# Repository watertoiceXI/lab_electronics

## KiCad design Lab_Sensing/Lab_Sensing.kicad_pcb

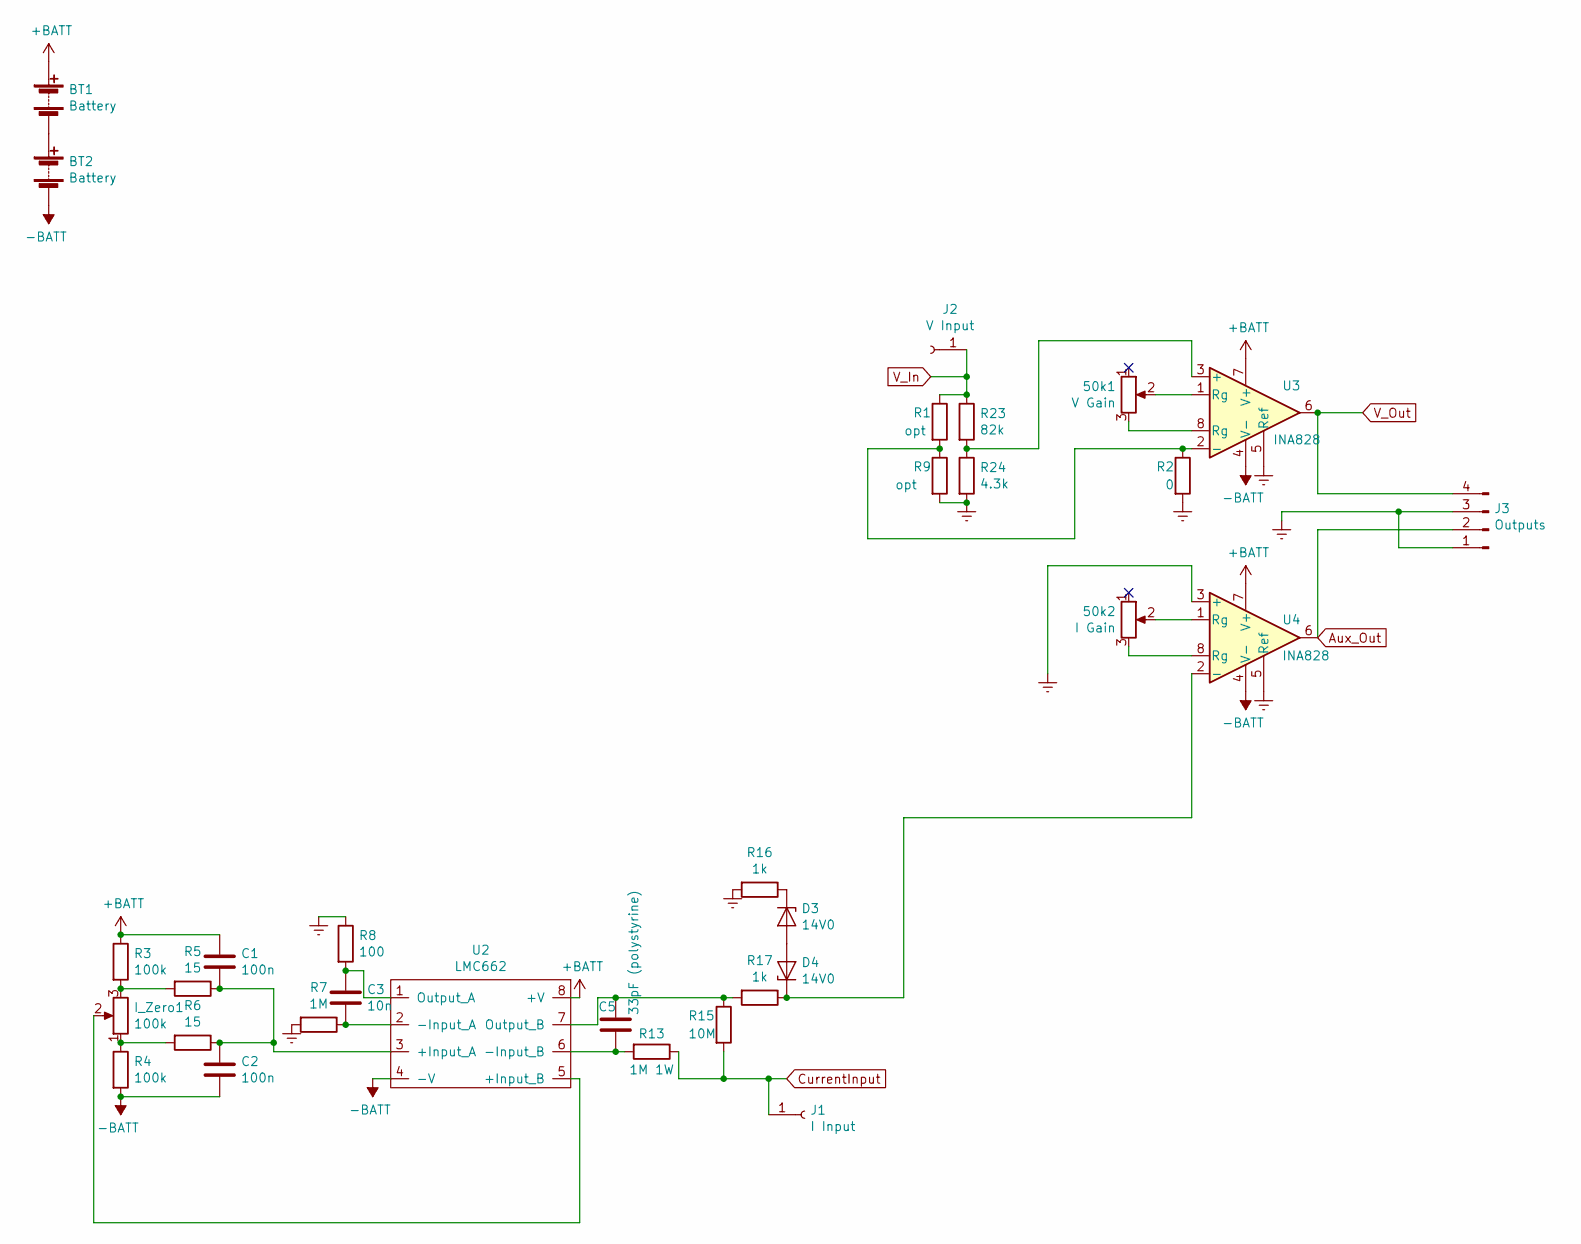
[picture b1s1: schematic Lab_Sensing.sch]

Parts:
50k1: V Gain; Potentiometer_Vishay_T73YP_Vertical
50k2: I Gain; Potentiometer_Vishay_T73YP_Vertical
BT1, BT2: Battery; SolderWirePad_1x02_P3.81mm_Drill1.2mm
C1, C2: 100n; C_0805_2012Metric_Pad1.15x1.40mm_HandSolder
C3: 10n; C_0805_2012Metric_Pad1.15x1.40mm_HandSolder
C5: 33pF (polystyrine); CP_Axial_L11.0mm_D5.0mm_P18.00mm_Horizontal
D3, D4: 14V0; D_SOD-123
I_Zero1: 100k; Potentiometer_Vishay_T73YP_Vertical
J1: I Input; PinHeader_1x01_P2.54mm_Vertical
J2: V Input; PinHeader_1x01_P2.54mm_Vertical
J3: Outputs; PinHeader_1x04_P2.54mm_Vertical
R1, R9: opt; R_Axial_DIN0207_L6.3mm_D2.5mm_P7.62mm_Horizontal
R2: 0; R_Axial_DIN0207_L6.3mm_D2.5mm_P7.62mm_Horizontal
R3, R4: 100k; R_0805_2012Metric
R5, R6: 15; R_0805_2012Metric
R7: 1M; R_0805_2012Metric
R8: 100; R_0805_2012Metric
R13: 1M 1W; R_Axial_DIN0617_L17.0mm_D6.0mm_P20.32mm_Horizontal
R15: 10M; R_Axial_DIN0207_L6.3mm_D2.5mm_P7.62mm_Horizontal
R16, R17: 1k; R_Axial_DIN0207_L6.3mm_D2.5mm_P7.62mm_Horizontal
R23: 82k; R_Axial_DIN0207_L6.3mm_D2.5mm_P7.62mm_Horizontal
R24: 4.3k; R_Axial_DIN0207_L6.3mm_D2.5mm_P7.62mm_Horizontal
U2: LMC662; SOIC-8_3.9x4.9mm_P1.27mm
U3, U4: INA828; SOIC-8_3.9x4.9mm_P1.27mm

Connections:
+BATT: BT1.1 (+), C1.1, R3.1, U2.8 (+V), U3.7 (V+), U4.7 (V+)
-BATT: BT2.2 (-), C2.2, R4.2, U2.4 (-V), U3.4 (V-), U4.4 (V-)
Aux_Out: J3.2, U4.6
CurrentInput: J1.1, R13.1, R15.2
Earth: J3.1, J3.3, R2.2, R7.2, R8.1, R9.2, R16.2, R24.2, U3.5 (Ref), U4.3 (+), U4.5 (Ref)
unnamed 6: 50k1.2, U3.1 (Rg); also elsewhere on the board
unnamed 7: 50k1.3, U3.8 (Rg); also elsewhere on the board
unnamed 9: 50k2.2, U4.1 (Rg); also elsewhere on the board
unnamed 10: 50k2.3, U4.8 (Rg); also elsewhere on the board
unnamed: BT1.2 (-), BT2.1 (+)
unnamed: C1.2, C2.1, R5.1, R6.1, U2.3 (+Input_A)
unnamed: C3.1, R8.2, U2.1 (Output_A)
unnamed: C3.2, R7.1, U2.2 (-Input_A)
unnamed: C5.1, R15.1, R17.2, U2.7 (Output_B)
unnamed: C5.2, R13.2, U2.6 (-Input_B)
unnamed: D3.1 (K), R16.1
unnamed: D3.2 (A), D4.2 (A)
unnamed: D4.1 (K), R17.1, U4.2 (-)
unnamed 20: I_Zero1.1, R4.1, R6.2; also elsewhere on the board
unnamed 21: I_Zero1.2, U2.5 (+Input_B); also elsewhere on the board
unnamed 22: I_Zero1.3, R3.2, R5.2; also elsewhere on the board
unnamed: R1.2, R2.1, R9.1, U3.2 (-)
unnamed: R23.2, R24.1, U3.3 (+)
V_In: J2.1, R1.1, R23.1
V_Out: J3.4, U3.6

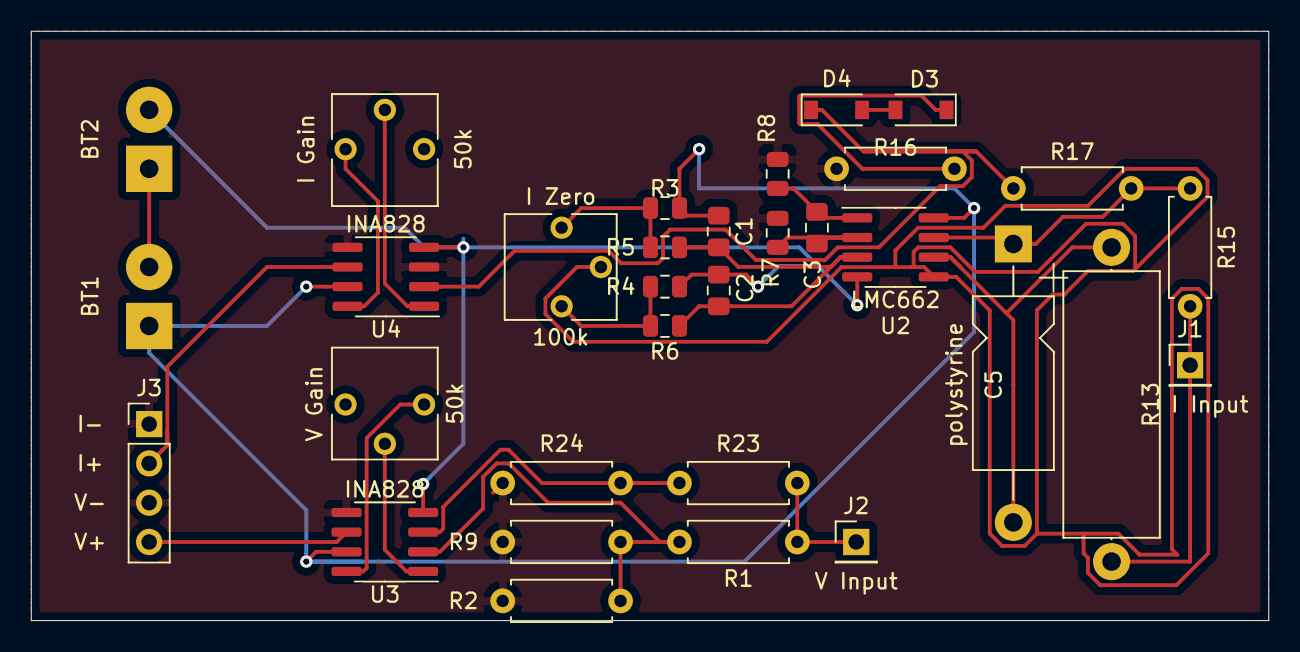
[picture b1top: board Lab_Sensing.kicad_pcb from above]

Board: 2 copper layers, 80.0 x 38.1 mm, 32 parts (0 on the bottom side), 25 nets.

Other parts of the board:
50k: V Gain; Potentiometer_Vishay_T73YP_Vertical
50k#2: I Gain; Potentiometer_Vishay_T73YP_Vertical
I Zero: 100k; Potentiometer_Vishay_T73YP_Vertical

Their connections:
unnamed 6: 50k.2; also elsewhere on the board
unnamed 7: 50k.3; also elsewhere on the board
unnamed 9: 50k#2.2; also elsewhere on the board
unnamed 10: 50k#2.3; also elsewhere on the board
unnamed 20: I Zero.1; also elsewhere on the board
unnamed 21: I Zero.2; also elsewhere on the board
unnamed 22: I Zero.3; also elsewhere on the board

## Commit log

2022-03-14 first commit, probably wrong in multiple ways. --jhp
